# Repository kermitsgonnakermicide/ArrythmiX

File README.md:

# Main Repo
This is the main repo for the Arryhtmix Project, which aims to develop a novel, end-to-end framework for
the prediction of caridiac events
>
> We have developed a novel end to end pipeline for the prediction of cardiac arrests through machine learning alongside a medical device to facilitate the collection of data for the model.
>
>The initial process takes place on the device. The single-lead AD8232 Sensor with integrated hardware high pass and low pass filters collects ECG Data from one lead with one electrode for common mode rejection. The data is read at a rate of 360 Hz by the nRF52840 using a 12-bit ADC and concurrently denoised through an integrated LSM6DS3. While the device is idle, it is kept in deep sleep mode, significantly reducing power consumption.
>Upon the collection of 10 data points, the buffer is dispatched using BLE to the host device.
>
>Upon being dispatched to the host device, two models are run on it. First, an Arrhythmia classification model based on the MIT-BIH dataset and architected with a BiLSTM and Random Forest classifier returns a dataclass which describes the type of arrhythmia if any. Secondly, a novel model based on the Sudden Cardiac Arrest Holter Database architected by DAKSH EXPLAIN HERE is implemented. This provides  a set of “risk classes” which give the probability of a heart attack happening in the specified timeframe. A f-score of 99 percent and of 85 percent is obtained from both models respectively.
> - ISEF Abstract
### Sections
- [Scripts](scripts)
  - scripts for interfacing and interaction with the device
- [Hardware](Hardware)
  - Device schematics, PCB Design etc.
- [Firmware](src)
  - firmware for the device
- [ML](ML)
  - machine learning stuff

### Images 

<br>
    
<br>

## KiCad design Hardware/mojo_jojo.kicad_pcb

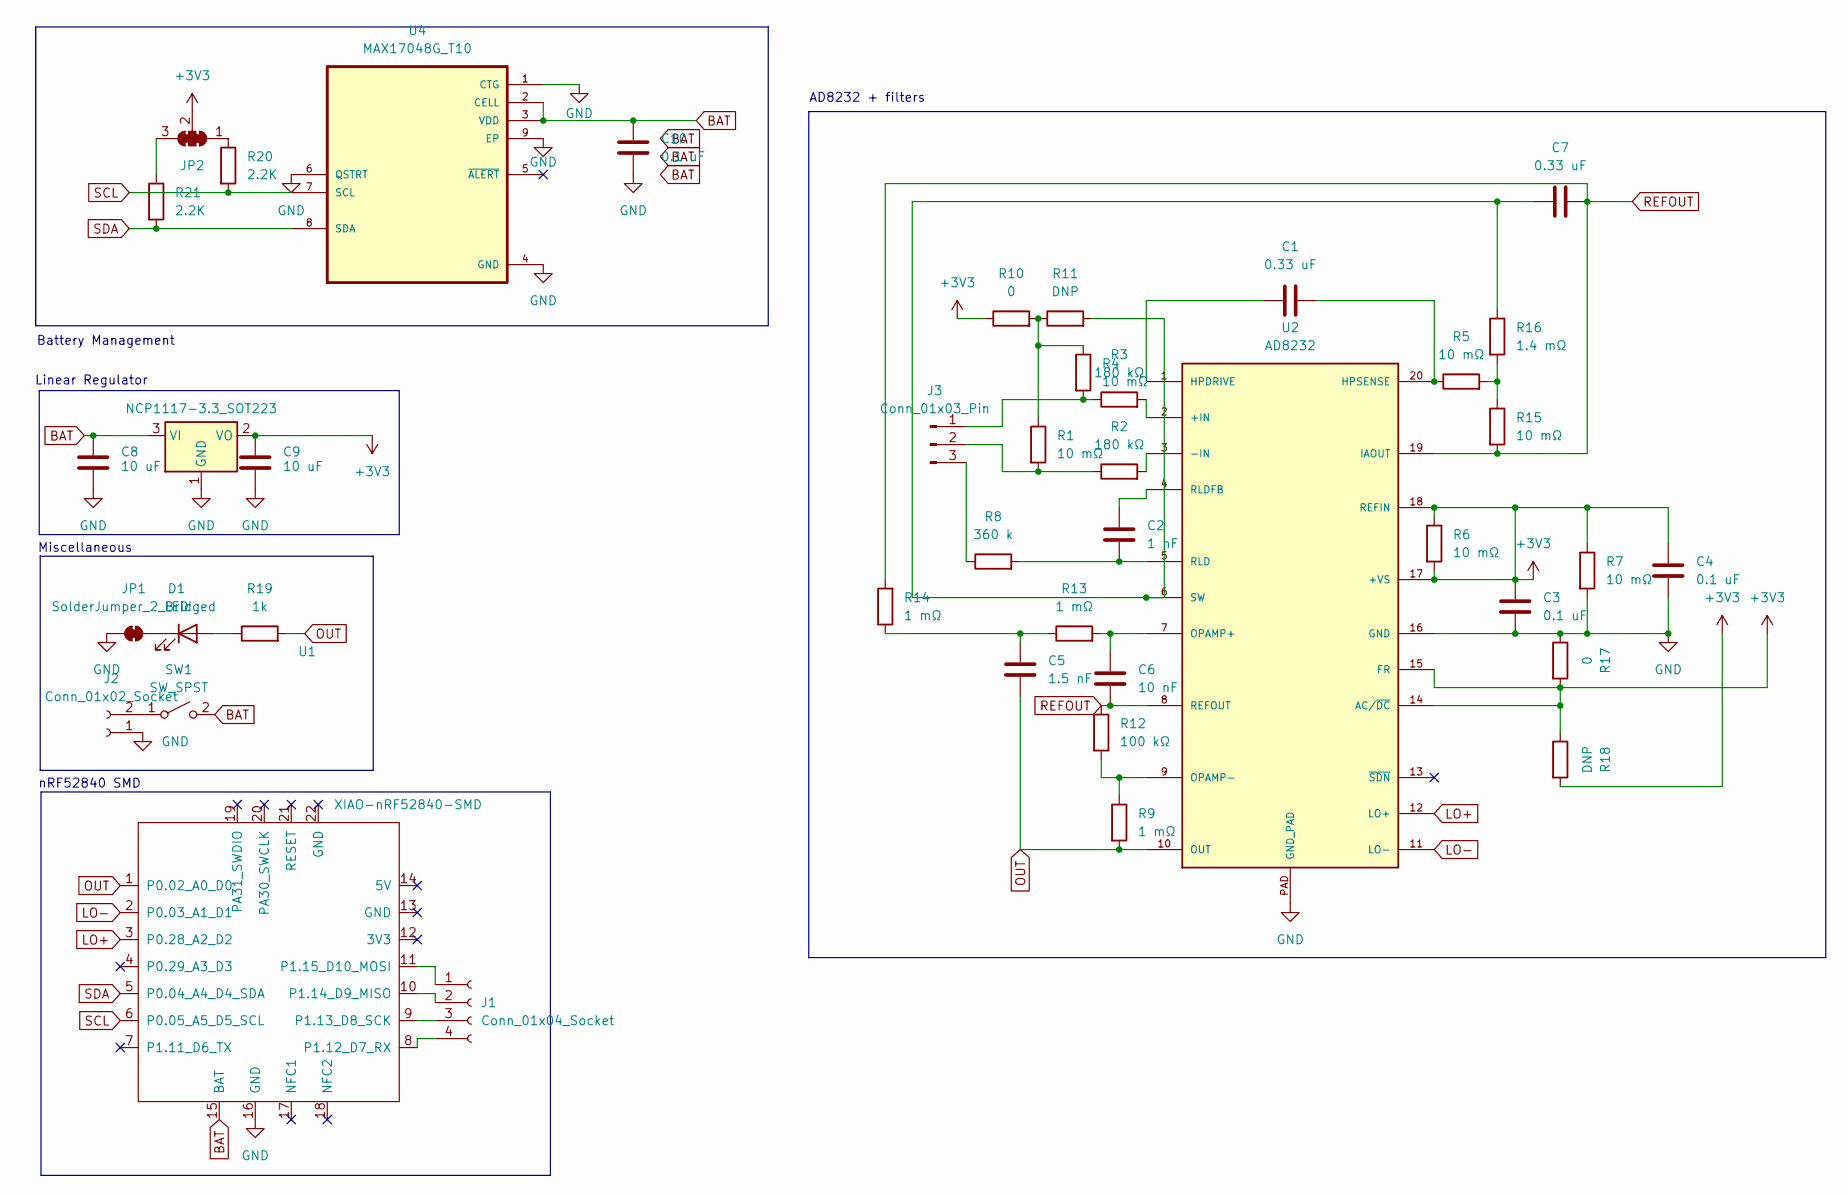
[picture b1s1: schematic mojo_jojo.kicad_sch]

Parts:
C1, C7: 0.33 uF; C_0201_0603Metric
C2: 1 nF; C_0201_0603Metric
C3, C4, C10: 0.1 uF; C_0201_0603Metric
C5: 1.5 nF; C_0201_0603Metric
C6: 10 nF; C_0201_0603Metric
C8, C9: 10 uF; C_0402_1005Metric
D1: LED; LED_0603_1608Metric
J1: Conn_01x04_Socket; PinSocket_1x04_P1.27mm_Vertical
J2: Conn_01x02_Socket; PinSocket_1x02_P2.54mm_Vertical
J3: Conn_01x03_Pin; PinHeader_1x03_P2.54mm_Vertical
JP1: SolderJumper_2_Bridged; SolderJumper-2_P1.3mm_Bridged2Bar_RoundedPad1.0x1.5mm
JP2: SolderJumper_3_Bridged123; SolderJumper-3_P1.3mm_Open_Pad1.0x1.5mm_NumberLabels
R1, R4, R5, R6, R7, R15: 10 mΩ; R_0201_0603Metric
R2, R3: 180 kΩ; R_0201_0603Metric
R8: 360 k; R_0201_0603Metric
R9, R13, R14: 1 mΩ; R_0201_0603Metric
R10, R17: 0; R_0201_0603Metric
R11, R18: DNP; R_0201_0603Metric
R12: 100 kΩ; R_0201_0603Metric
R16: 1.4 mΩ; R_0201_0603Metric
R19: 1k; R_0201_0603Metric
R20, R21: 2.2K; R_0402_1005Metric
SW1: SW_SPST; SW_DIP_SPSTx01_Slide_6.7x4.1mm_W6.73mm_P2.54mm_LowProfile_J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
U1: XIAO-nRF52840-SMD
U2: AD8232; LFCSP_20
U3: NCP1117-3.3_SOT223; SOT-223-3_TabPin2
U4: MAX17048G_T10; SON50P200X200X80-9N

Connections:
+3V3: C3.2, C4.2, C9.1, JP2.2 (C), R6.1, R6.2, R7.1, R10.1, R17.2, R18.1, R18.2, U2.14 (AC/~DC), U2.15 (FR), U2.17 (+VS), U2.18 (REFIN), U3.2 (VO); also elsewhere on the board
BAT: C8.1, C10.2, SW1.2 (B), U1.15 (BAT), U3.3 (VI), U4.2 (CELL), U4.3 (VDD)
GND: C3.1, C4.1, C8.2, C9.2, C10.1, J2.1, JP1.1 (A), R7.2, R17.1, U1.16 (GND), U2.16 (GND), U2.PAD (GND_PAD), U3.1 (GND), U4.1 (CTG), U4.4 (GND), U4.6 (QSTRT), U4.9 (EP); also elsewhere on the board
LO+: U1.3 (P0.28_A2_D2), U2.12 (LO+)
LO-: U1.2 (P0.03_A1_D1), U2.11 (LO-)
unnamed: C5.2, R13.1, R14.1
unnamed: D1.2 (A), R19.1
unnamed 7: D1.1 (K), JP1.2 (B); also elsewhere on the board
unnamed: J1.1, U1.11 (P1.15_D10_MOSI)
unnamed: J1.2, U1.10 (P1.14_D9_MISO)
unnamed: J1.3, U1.9 (P1.13_D8_SCK)
unnamed: J1.4, U1.8 (P1.12_D7_RX)
unnamed: J2.2, SW1.1 (A)
unnamed: J3.1, R3.1, R4.2
unnamed: J3.2, R1.2, R2.1
unnamed: J3.3, R8.1
unnamed: JP2.1 (A), R20.1
unnamed: JP2.3 (B), R21.1
unnamed: R1.1, R4.1, R10.2, R11.1
unnamed: R5.2, R15.1, R16.2
unnamed: R3.2, U2.2 (+IN)
unnamed: R2.2, U2.3 (-IN)
unnamed: C1.1, U2.1 (HPDRIVE)
unnamed: C1.2, R5.1, U2.20 (HPSENSE)
unnamed: C6.2, R13.2, U2.7 (OPAMP+)
unnamed: R9.1, R12.2, U2.9 (OPAMP-)
unnamed: C2.2, R8.2, U2.5 (RLD)
unnamed: C2.1, U2.4 (RLDFB)
unnamed: C7.1, R11.2, R16.1, U2.6 (SW)
OUT: C5.1, R9.2, R19.2, U1.1 (P0.02_A0_D0), U2.10 (OUT)
REFOUT: C6.1, C7.2, R12.1, R14.2, R15.2, U2.8 (REFOUT), U2.19 (IAOUT)
SCL: R20.2, U1.6 (P0.05_A5_D5_SCL), U4.7 (SCL)
SDA: R21.2, U1.5 (P0.04_A4_D4_SDA), U4.8 (SDA)

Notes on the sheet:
nRF52840 SMD
AD8232 + filters
Miscellaneous
Linear Regulator
Battery Management

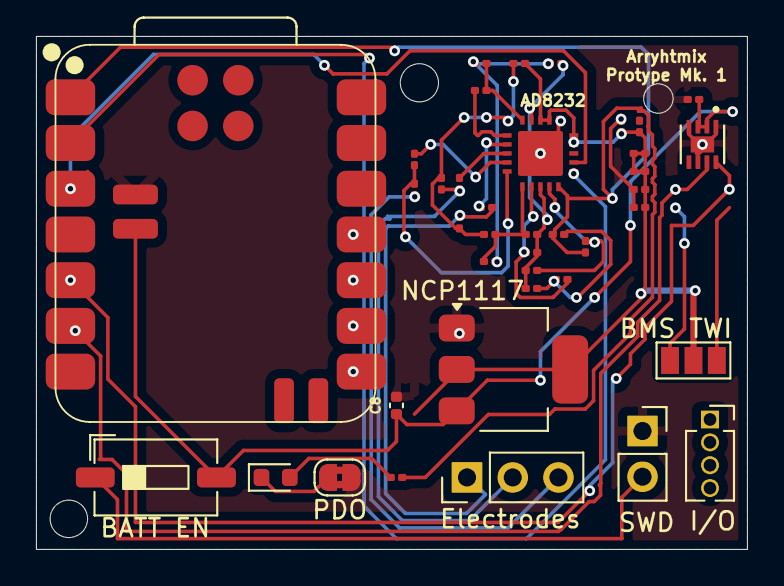
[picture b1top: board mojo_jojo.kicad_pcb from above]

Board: 4 copper layers, 39.5 x 28.5 mm, 40 parts (1 on the bottom side), 31 nets.

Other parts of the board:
BMS TWI: SolderJumper_3_Bridged123; SolderJumper-3_P1.3mm_Open_Pad1.0x1.5mm_NumberLabels
PDO: SolderJumper_2_Bridged; SolderJumper-2_P1.3mm_Bridged2Bar_RoundedPad1.0x1.5mm

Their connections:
+3V3: BMS TWI.2 (C); also elsewhere on the board
GND: PDO.1 (A); also elsewhere on the board
unnamed 7: PDO.2 (B); also elsewhere on the board

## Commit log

2025-08-26 aaaaaaaaaaaaaaaaaaaaaaaaaaaaaaaaaaaaaaaa
2025-10-08 add nrf52840 code
2025-10-08 add python scripts
2025-10-13 add latest ML, dashboard stuff
2025-10-14 long long years of suffering past
2025-10-30 Created using Colab
2025-11-07 sleep instead of busy waiting for better power consumption, need to transmit IMU
2025-11-07 add buffering
2025-11-14 cleanup repo, add README.md
2025-11-14 w
    w
2025-11-17 setup basic zephyr functionality
2025-11-19 adc readring
2025-11-19 i cooked
2025-11-23 add pcb files
